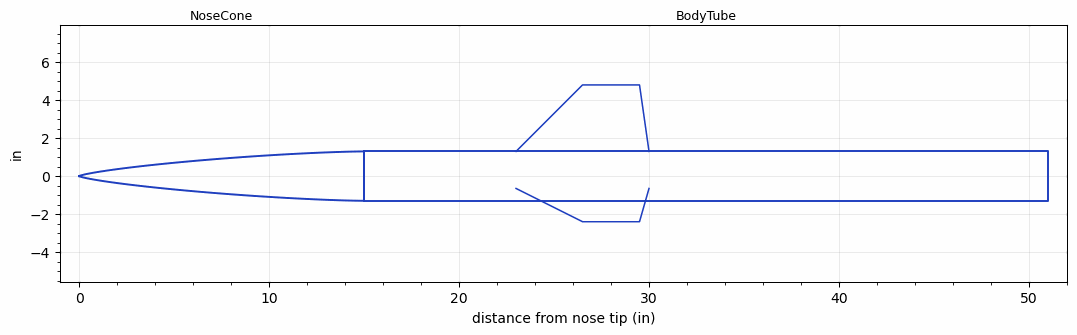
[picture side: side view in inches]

<RASAeroDocument>
 <FileVersion>2</FileVersion>
 <RocketDesign>
  <NoseCone>
   <Length>15</Length>
   <Diameter>2.6</Diameter>
   <Shape>Von Karman Ogive</Shape>
   <Location>0</Location>
  </NoseCone>
  <BodyTube>
   <Length>36</Length>
   <Diameter>2.6</Diameter>
   <LaunchLugDiameter>0.375</LaunchLugDiameter>
   <LaunchLugLength>1.5</LaunchLugLength>
   <Location>15</Location>
   <Fin>
    <Count>3</Count>
    <Chord>7</Chord>
    <Span>3.5</Span>
    <SweepDistance>3.5</SweepDistance>
    <TipChord>3</TipChord>
    <Thickness>0.125</Thickness>
    <Location>28</Location>
    <AirfoilSection>Square</AirfoilSection>
   </Fin>
  </BodyTube>
  <Surface>Smooth Paint</Surface>
  <ModifiedBarrowman>False</ModifiedBarrowman>
  <Comments>Loft demo — 66 mm sport (RASAero)</Comments>
 </RocketDesign>
 <LaunchSite>
  <Altitude>200</Altitude>
  <Pressure>29.92</Pressure>
  <RodAngle>0</RodAngle>
  <RodLength>6</RodLength>
  <Temperature>59</Temperature>
  <WindSpeed>5</WindSpeed>
 </LaunchSite>
 <Recovery>
  <DeviceType1>Parachute</DeviceType1>
  <Size1>3</Size1>
  <CD1>1.33</CD1>
  <Altitude1>0</Altitude1>
  <DeviceType2>None</DeviceType2>
  <Size2>1</Size2>
  <CD2>1.33</CD2>
  <Altitude2>700</Altitude2>
 </Recovery>
 <SimulationList>
  <Simulation>
   <SustainerEngine>H128W  (AT)</SustainerEngine>
   <SustainerLaunchWt>3.9</SustainerLaunchWt>
   <SustainerCG>32.5</SustainerCG>
   <SustainerIgnitionDelay>0</SustainerIgnitionDelay>
   <TimetoApogee>9.4</TimetoApogee>
   <MaxAltitude>1420</MaxAltitude>
   <MaxVelocity>420</MaxVelocity>
  </Simulation>
 </SimulationList>
</RASAeroDocument>
